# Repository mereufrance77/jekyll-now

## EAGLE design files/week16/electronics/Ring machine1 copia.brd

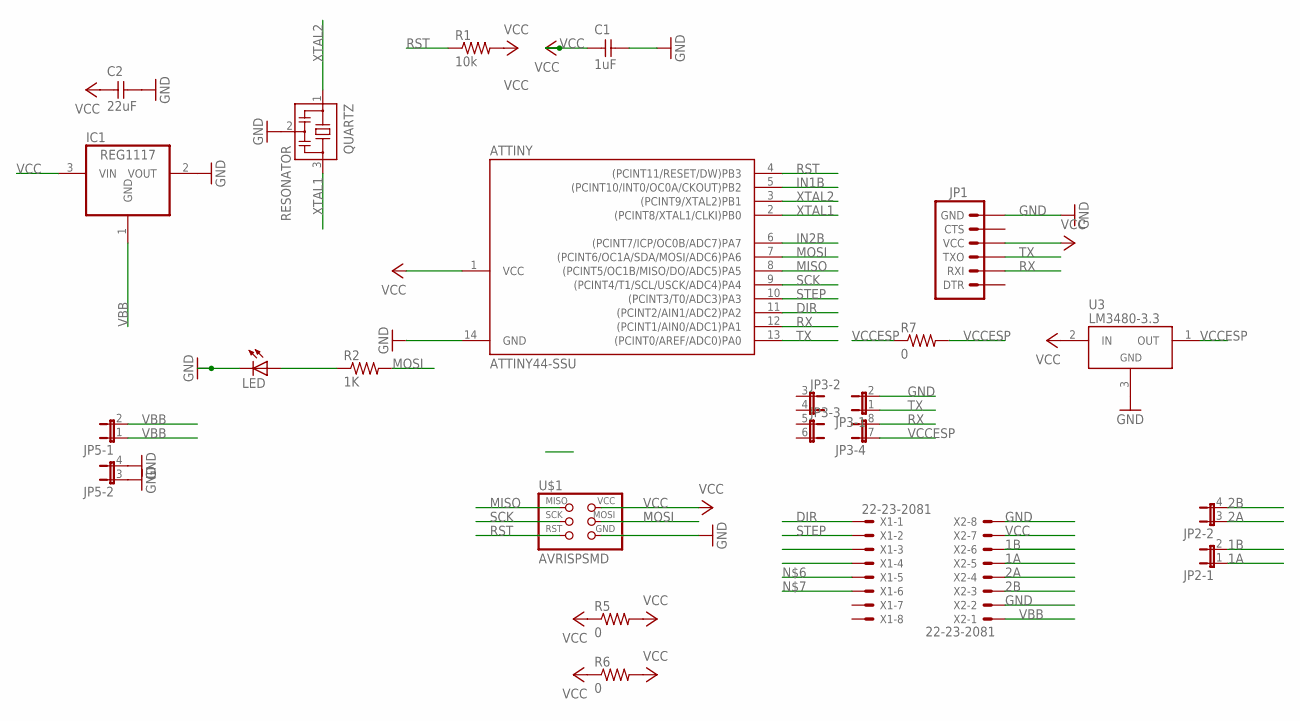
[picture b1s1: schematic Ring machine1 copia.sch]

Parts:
ATTINY: ATTINY44-SSU; SOIC14
C1: 1uF; 1206
C2: 22uF; 1206
IC1: REG1117; SOT223
JP1: ARDUINO_SERIAL_PROGRAMLONGPADS; 1X06_LONGPADS
JP2, JP5: JP2QE; JP2Q
JP3: JP4QE; JP4Q
LED: LED1206; 1206
QUARTZ: RESONATOR; EFOBM
R1: 10k; 1206
R2: 1K; 1206
R5, R6, R7: 0; 1206
U3: LM3480-3.3; SOT-23-3
U$1: AVRISPSMD; 2X03SMD
X1, X2: 22-23-2081

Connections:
1A: JP2.1, X2.5
1B: JP2.2, X2.6
2A: JP2.3 (1), X2.4
2B: JP2.4 (2), X2.3
DIR: ATTINY.11 ((PCINT2/AIN1/ADC2)PA2), X1.1
GND: ATTINY.14 (GND), C1.2, C2.2, IC1.2 (VOUT), JP1.6 (GND), JP3.2, JP5.3 (1), JP5.4 (2), LED.2 (C), QUARTZ.2, U3.3 (GND), U$1.6 (GND), X2.2, X2.8
IN1B: ATTINY.5 ((PCINT10/INT0/OC0A/CKOUT)PB2)
IN2B: ATTINY.6 ((PCINT7/ICP/OC0B/ADC7)PA7)
LEDRES: LED.1 (A), R2.1
MISO: ATTINY.8 ((PCINT5/OC1B/MISO/DO/ADC5)PA5), U$1.1 (MISO)
MOSI: ATTINY.7 ((PCINT6/OC1A/SDA/MOSI/ADC6)PA6), R2.2, U$1.4 (MOSI)
RST: ATTINY.4 ((PCINT11/RESET/DW)PB3), R1.1, U$1.5 (RST)
RX: ATTINY.12 ((PCINT1/AIN0/ADC1)PA1), JP1.2 (RXI), JP3.8 (2)
SCK: ATTINY.9 ((PCINT4/T1/SCL/USCK/ADC4)PA4), U$1.3 (SCK)
STEP: ATTINY.10 ((PCINT3/T0/ADC3)PA3), X1.2
TX: ATTINY.13 ((PCINT0/AREF/ADC0)PA0), JP1.3 (TXO), JP3.1
VBB: IC1.1 (GND), JP5.1, JP5.2, X2.1
VCC: ATTINY.1 (VCC), C1.1, C2.1, IC1.3 (VIN), JP1.4 (VCC), R1.2, R5.1, R5.2, R6.1, R6.2, U3.2 (IN), U$1.2 (VCC), X2.7
VCCESP: JP3.7 (1), R7.1, R7.2, U3.1 (OUT)
XTAL1: ATTINY.2 ((PCINT8/XTAL1/CLKI)PB0), QUARTZ.3
XTAL2: ATTINY.3 ((PCINT9/XTAL2)PB1), QUARTZ.1

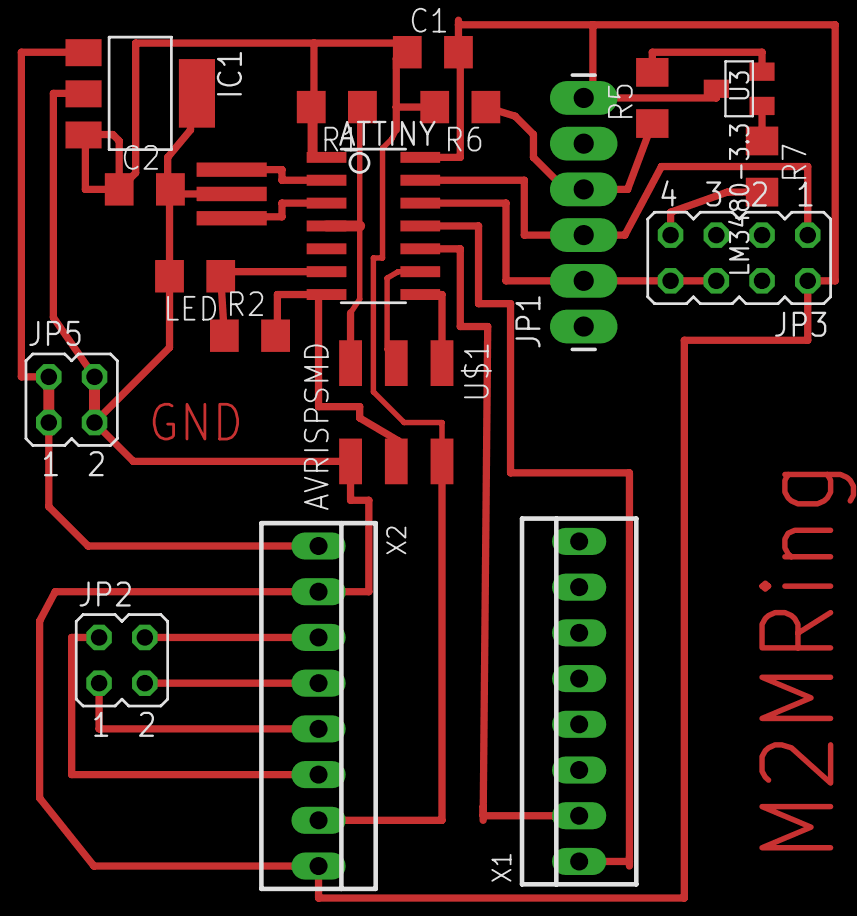
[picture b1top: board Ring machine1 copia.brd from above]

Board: 2 copper layers, 19 parts (0 on the bottom side), 19 nets.

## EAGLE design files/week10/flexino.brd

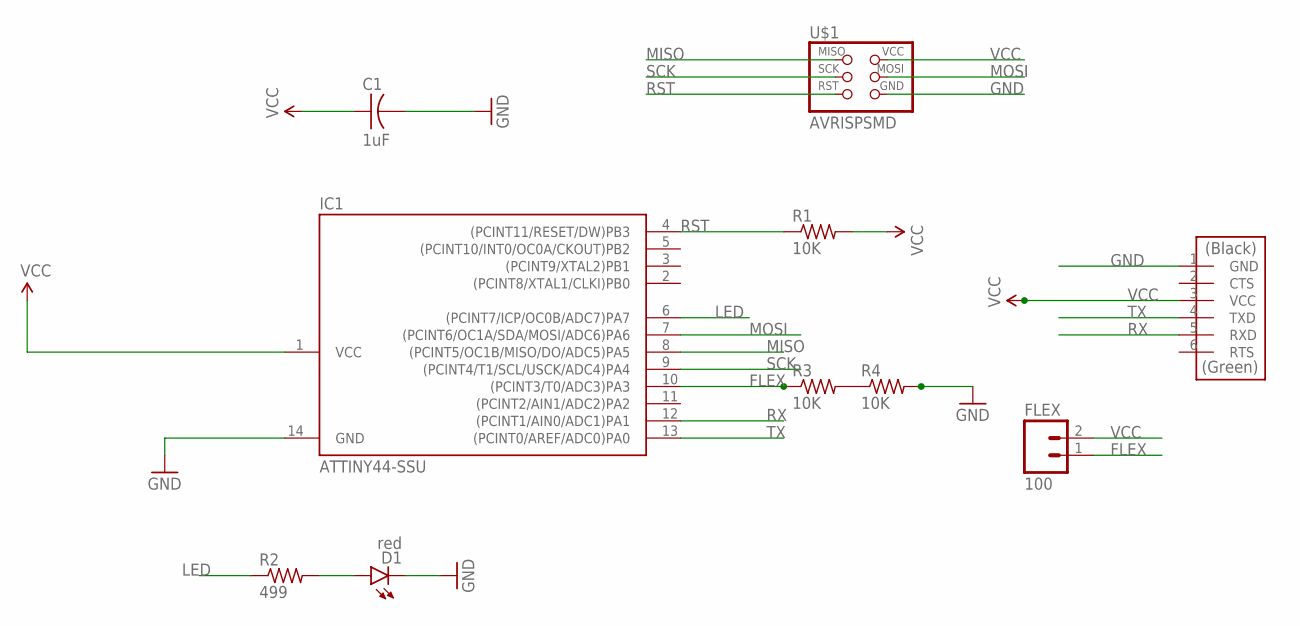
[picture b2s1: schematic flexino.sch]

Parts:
C1: 1uF; C1206FAB
D1: red; LED-1206
FLEX: 100; 1X02_LONGPADS
IC1: ATTINY44-SSU; SOIC14
R1, R3, R4: 10K; R1206W
R2: 499; R1206W
U$1: AVRISPSMD; 2X03SMD
U$2: FTDI-SMD-HEADER; 1X06SMD

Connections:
FLEX: FLEX.1, IC1.10 ((PCINT3/T0/ADC3)PA3), R3.1
GND: C1.2, D1.C, IC1.14 (GND), R4.2, U$1.6 (GND), U$2.1 (GND)
LED: IC1.6 ((PCINT7/ICP/OC0B/ADC7)PA7), R2.1
MISO: IC1.8 ((PCINT5/OC1B/MISO/DO/ADC5)PA5), U$1.1 (MISO)
MOSI: IC1.7 ((PCINT6/OC1A/SDA/MOSI/ADC6)PA6), U$1.4 (MOSI)
unnamed: D1.A, R2.2
unnamed: R3.2, R4.1
RST: IC1.4 ((PCINT11/RESET/DW)PB3), R1.1, U$1.5 (RST)
RX: IC1.12 ((PCINT1/AIN0/ADC1)PA1), U$2.5 (RXD)
SCK: IC1.9 ((PCINT4/T1/SCL/USCK/ADC4)PA4), U$1.3 (SCK)
TX: IC1.13 ((PCINT0/AREF/ADC0)PA0), U$2.4 (TXD)
VCC: C1.1, FLEX.2, IC1.1 (VCC), R1.2, U$1.2 (VCC), U$2.3 (VCC)

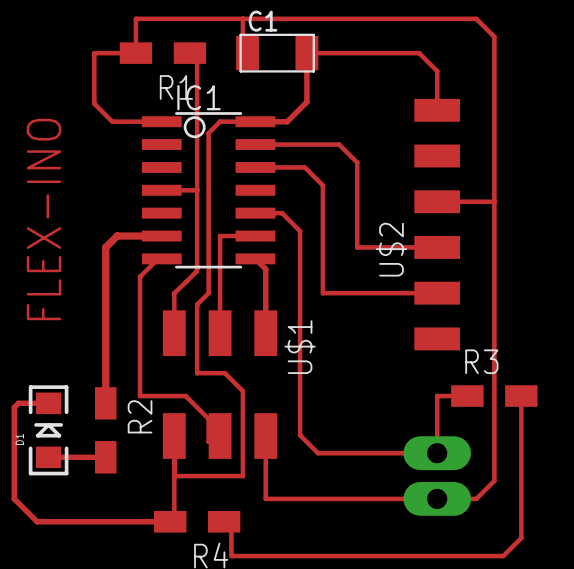
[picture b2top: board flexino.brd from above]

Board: 2 copper layers, 10 parts (0 on the bottom side), 12 nets.

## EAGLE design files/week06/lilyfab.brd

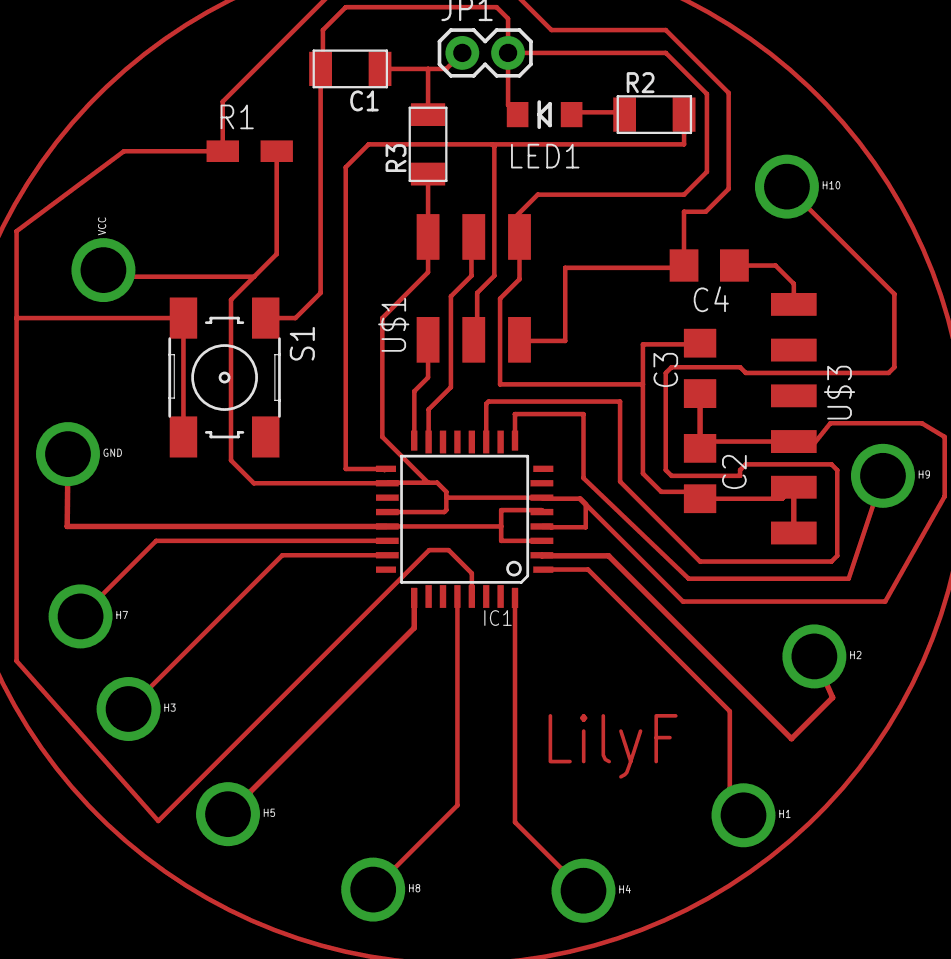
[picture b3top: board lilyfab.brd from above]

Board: 2 copper layers, 24 parts (0 on the bottom side), 18 nets.

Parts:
C1: 4uF; C1206FAB
C2: 1.0uF; C1206
C3: 0.1 uF; C1206
C4: 0.1uF; C1206
GND: SEW_HOLE; SIMPLE_HOLE
H1, H2, H3, H4, H5, H7, H8, H9, H10: SEW_HOLE; SIMPLE_HOLE
IC1: ATMEGA88-THIN; TQFP32-08THIN
JP1: 1X02
LED1: LED-1206
R1: 10K; R1206W
R2: 330; R1206FAB
R3: 0; R1206FAB
S1: 6MM_SWITCH
U$1: AVRISPSMD; 2X03SMD
U$3: FTDI-SMD-HEADER; 1X06SMD
VCC: SEW_HOLE; SIMPLE_HOLE

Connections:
GND: C1.2, C2.2, C3.2, JP1.2, LED1.C, S1.1, U$1.6, U$3.1, U$3.2
MISO: IC1.16, U$1.1
MOSI: IC1.15, U$1.4
unnamed: H3.P$1, IC1.23
unnamed: H7.P$1, IC1.22
unnamed: LED1.A, R2.1
unnamed: H5.P$1, IC1.25
unnamed: H8.P$1, IC1.28
unnamed: H4.P$1, IC1.32
unnamed: H1.P$1, IC1.1
unnamed: H2.P$1, IC1.2
unnamed: H9.P$1, IC1.9
unnamed: H10.P$1, IC1.11
unnamed: GND.P$1, IC1.3, IC1.5, IC1.21
RST: C4.2, IC1.29, R1.1, S1.3, S1.4, U$1.5
RTS: C4.1, U$3.6
SCK: IC1.17, R2.2, U$1.3
VCC: C1.1, C2.1, C3.1, IC1.4, IC1.6, IC1.18, IC1.20, JP1.1, R1.2, R3.1, R3.2, U$1.2, U$3.3, VCC.P$1

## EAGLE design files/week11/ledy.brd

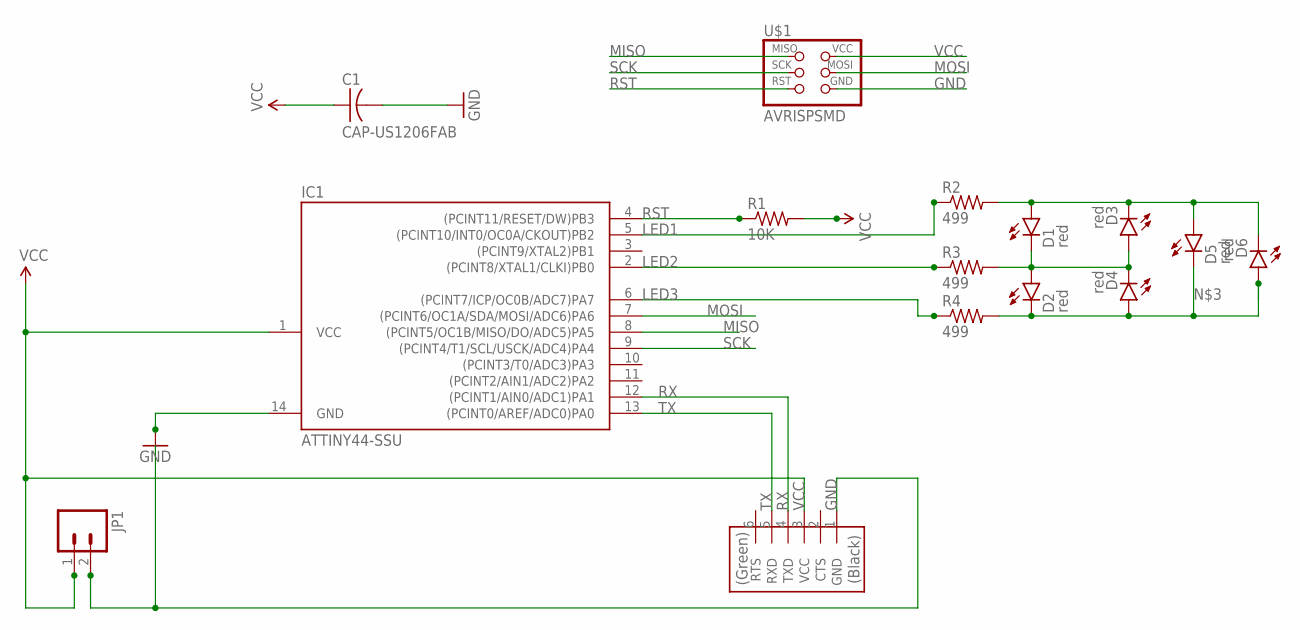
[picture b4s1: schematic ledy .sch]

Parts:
C1: CAP-US1206FAB; C1206FAB
D1, D2, D3, D4, D5, D6: red; LED-1206
IC1: ATTINY44-SSU; SOIC14
JP1: M02PTH; 1X02
R1: 10K; R1206W
R2, R3, R4: 499; R1206W
U$1: AVRISPSMD; 2X03SMD
U$3: FTDI-SMD-HEADER; 1X06SMD

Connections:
GND: C1.2, IC1.14 (GND), JP1.2, U$1.6 (GND), U$3.1 (GND)
LED1: IC1.5 ((PCINT10/INT0/OC0A/CKOUT)PB2), R2.1
LED2: R3.1
LED3: IC1.6 ((PCINT7/ICP/OC0B/ADC7)PA7), R4.1
MISO: IC1.8 ((PCINT5/OC1B/MISO/DO/ADC5)PA5), U$1.1 (MISO)
MOSI: IC1.7 ((PCINT6/OC1A/SDA/MOSI/ADC6)PA6), U$1.4 (MOSI)
unnamed: D1.A, D3.C, D5.A, D6.C, R2.2
unnamed: D2.C, D4.A, D5.C, D6.A, R4.2
unnamed: D1.C, D2.A, D3.A, D4.C, R3.2
RST: IC1.4 ((PCINT11/RESET/DW)PB3), R1.1, U$1.5 (RST)
RX: IC1.12 ((PCINT1/AIN0/ADC1)PA1), U$3.4 (TXD)
SCK: IC1.9 ((PCINT4/T1/SCL/USCK/ADC4)PA4), U$1.3 (SCK)
TX: IC1.13 ((PCINT0/AREF/ADC0)PA0), U$3.5 (RXD)
VCC: C1.1, IC1.1 (VCC), JP1.1, R1.2, U$1.2 (VCC), U$3.3 (VCC)

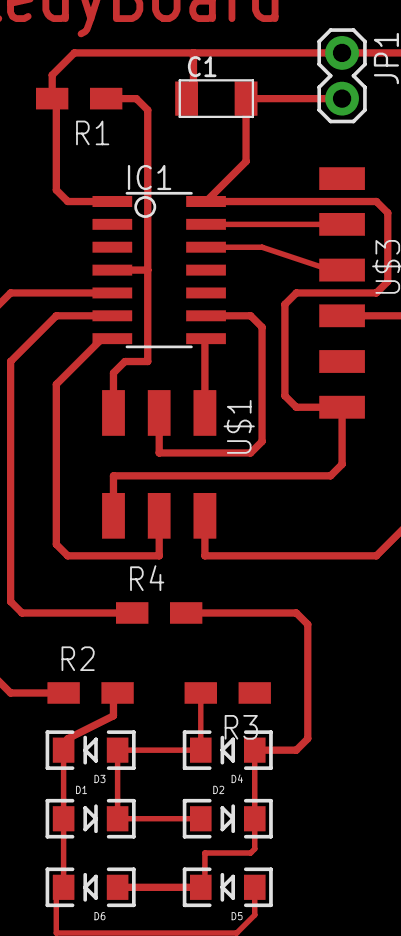
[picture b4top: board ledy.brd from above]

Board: 2 copper layers, 15 parts (0 on the bottom side), 13 nets.

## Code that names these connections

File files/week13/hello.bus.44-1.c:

//
//
// hello.bus.44.c
//
// 9600 baud serial bus hello-world
//
// Neil Gershenfeld
// 11/24/10
//
// (c) Massachusetts Institute of Technology 2010
// Permission granted for experimental and personal use;
// license for commercial sale available from MIT.
//

#include <avr/io.h>
#include <util/delay.h>
#include <avr/pgmspace.h>
#include <string.h>

#define output(directions,pin) (directions |= pin) // set port direction for output
#define input(directions,pin) (directions &= (~pin)) // set port direction for input
#define set(port,pin) (port |= pin) // set port pin
#define clear(port,pin) (port &= (~pin)) // clear port pin
#define pin_test(pins,pin) (pins & pin) // test for port pin
#define bit_test(byte,bit) (byte & (1 << bit)) // test for bit set
#define bit_delay_time 100 // bit delay for 9600 with overhead
#define bit_delay() _delay_us(bit_delay_time) // RS232 bit delay
#define half_bit_delay() _delay_us(bit_delay_time/2) // RS232 half bit delay
#define led_delay() _delay_ms(100) // LED flash delay

#define led_port PORTA
#define led_direction DDRA
#define led_pin (1 << PA7)

#define serial_port PORTB
#define serial_direction DDRB
#define serial_pins PINB
#define serial_pin_in (1 << PB0)
#define serial_pin_out (1 << PB1)

#define node_id '1'

void get_char(volatile unsigned char *pins, unsigned char pin, char *rxbyte) {
   //
   // read character into rxbyte on pins pin
   //    assumes line driver (inverts bits)
   //
   *rxbyte = 0;
   while (pin_test(*pins,pin))
      //
      // wait for start bit
      //
      ;
   //
   // delay to middle of first data bit
   //
   half_bit_delay();
   bit_delay();
   //
   // unrolled loop to read data bits
   //
   if pin_test(*pins,pin)
      *rxbyte |= (1 << 0);
   else
      *rxbyte |= (0 << 0);
   bit_delay();
   if pin_test(*pins,pin)
      *rxbyte |= (1 << 1);
   else
      *rxbyte |= (0 << 1);
   bit_delay();
   if pin_test(*pins,pin)
      *rxbyte |= (1 << 2);
   else
      *rxbyte |= (0 << 2);
   bit_delay();
   if pin_test(*pins,pin)
      *rxbyte |= (1 << 3);
   else
      *rxbyte |= (0 << 3);
   bit_delay();
   if pin_test(*pins,pin)
      *rxbyte |= (1 << 4);
   else
      *rxbyte |= (0 << 4);
   bit_delay();
   if pin_test(*pins,pin)
      *rxbyte |= (1 << 5);
   else
      *rxbyte |= (0 << 5);
   bit_delay();
   if pin_test(*pins,pin)
      *rxbyte |= (1 << 6);
   else
      *rxbyte |= (0 << 6);
   bit_delay();
   if pin_test(*pins,pin)
      *rxbyte |= (1 << 7);
   else
      *rxbyte |= (0 << 7);
   //
   // wait for stop bit
   //
   bit_delay();
   half_bit_delay();
   }

void put_char(volatile unsigned char *port, unsigned char pin, char txchar) {
   //
   // send character in txchar on port pin
   //    assumes line driver (inverts bits)
   //
   // start bit
   //
   clear(*port,pin);
   bit_delay();
   //
   // unrolled loop to write data bits
   //
   if bit_test(txchar,0)
      set(*port,pin);
   else
      clear(*port,pin);
   bit_delay();
   if bit_test(txchar,1)
      set(*port,pin);
   else
      clear(*port,pin);
   bit_delay();
   if bit_test(txchar,2)
      set(*port,pin);
   else
      clear(*port,pin);
   bit_delay();
   if bit_test(txchar,3)
      set(*port,pin);
   else
      clear(*port,pin);
   bit_delay();
   if bit_test(txchar,4)
      set(*port,pin);
   else
      clear(*port,pin);
   bit_delay();
   if bit_test(txchar,5)
      set(*port,pin);
   else
      clear(*port,pin);
   bit_delay();
   if bit_test(txchar,6)
      set(*port,pin);
   else
      clear(*port,pin);
   bit_delay();
   if bit_test(txchar,7)
      set(*port,pin);
   else
      clear(*port,pin);
   bit_delay();
   //
   // stop bit
   //
   set(*port,pin);
   bit_delay();
   //
   // char delay
   //
   bit_delay();
   }

void put_string(volatile unsigned char *port, unsigned char pin, PGM_P str) {
   //
   // send character in txchar on port pin
   //    assumes line driver (inverts bits)
   //
   static char chr;
   static int index;
   index = 0;//
//
// hello.Flex.44.c
//
// flex sensor hello-world
//    9600 baud FTDI interface
//
// Francesca Mereu
// 10/05/15
//
// (c) Massachusetts Institute of Technology 2015
// This work may be reproduced, modified, distributed,
// performed, and displayed for any purpose. Copyright is
// retained and must be preserved. The work is provided
// as is; no warranty is provided, and users accept all 
// liability.
//

#include <avr/io.h>
#include <util/delay.h>

#define output(directions,pin) (directions |= pin) // set port direction for output
#define set(port,pin) (port |= pin) // set port pin
#define clear(port,pin) (port &= (~pin)) // clear port pin
#define pin_test(pins,pin) (pins & pin) // test for port pin
#define bit_test(byte,bit) (byte & (1 << bit)) // test for bit set
#define bit_delay_time 102 // bit delay for 9600 with overhead
#define bit_delay() _delay_us(bit_delay_time) // RS232 bit delay
#define half_bit_delay() _delay_us(bit_delay_time/2) // RS232 half bit delay
#define char_delay() _delay_ms(10) // char delay

#define serial_port PORTA
#define serial_direction DDRA
#define serial_pin_out (1 << PA3)

void put_char(volatile unsigned char *port, unsigned char pin, char txchar) {
   //
   // send character in txchar on port pin
   //    assumes line driver (inverts bits)
   //
   // start bit
   //
   clear(*port,pin);
   bit_delay();
   //
   // unrolled loop to write data bits
   //
   if bit_test(txchar,0)
      set(*port,pin);
   else
      clear(*port,pin);
   bit_delay();
   if bit_test(txchar,1)
      set(*port,pin);
   else
      clear(*port,pin);
   bit_delay();
   if bit_test(txchar,2)
      set(*port,pin);
   else
      clear(*port,pin);
   bit_delay();
   if bit_test(txchar,3)
      set(*port,pin);
   else
      clear(*port,pin);
   bit_delay();
   if bit_test(txchar,4)
      set(*port,pin);
   else
      clear(*port,pin);
   bit_delay();
   if bit_test(txchar,5)
      set(*port,pin);
   else
      clear(*port,pin);
   bit_delay();
   if bit_test(txchar,6)
      set(*port,pin);
   else
      clear(*port,pin);
   bit_delay();
   if bit_test(txchar,7)
      set(*port,pin);
   else
      clear(*port,pin);
   bit_delay();
   //
   // stop bit
   //
   set(*port,pin);
   bit_delay();
   //
   // char delay
   //
   bit_delay();
   }

int main(void) {
   //
   // main
   //
   static char chr;
   //
   // set clock divider to /1
   //
   CLKPR = (1 << CLKPCE);
   CLKPR = (0 << CLKPS3) | (0 << CLKPS2) | (0 << CLKPS1) | (0 << CLKPS0);
   //
   // initialize output pins
   //
   set(serial_port, serial_pin_out);
   output(serial_direction, serial_pin_out);
   //
   // init A/D
   //
   ADMUX = (0 << REFS1) | (0 << REFS0) // Vcc ref
      | (0 << ADLAR) // right adjust
      |(0 << MUX5) | (0 << MUX4) | (0 << MUX3) | (0 << MUX2) | (1 << MUX1) | (1 << MUX0); // ADC3
   ADCSRA = (1 << ADEN) // enable
      | (1 << ADPS2) | (1 << ADPS1) | (1 << ADPS0); // prescaler /128
   //
   // main loop
   //
   while (1) {
      //
      // send framing
      //
      put_char(&serial_port, serial_pin_out, 1);
      char_delay();
      put_char(&serial_port, serial_pin_out, 2);
      char_delay();
      put_char(&serial_port, serial_pin_out, 3);
      char_delay();
      put_char(&serial_port, serial_pin_out, 4);
      char_delay();
      //
      // initiate conversion
      //
      ADCSRA |= (1 << ADSC);
      //
      // wait for completion
      //
      while (ADCSRA & (1 << ADSC))
         ;
      //
      // send result
      //
      chr = ADCL;
      put_char(&serial_port, serial_pin_out, chr);
      char_delay();
      chr = ADCH;
      put_char(&serial_port, serial_pin_out, chr);
      char_delay();
      }
   }

   do {
      chr = pgm_read_byte(&(str[index]));
      put_char(&serial_port, serial_pin_out, chr);
      ++index;
      } while (chr != 0);
   }

void flash() {
   //
   // LED flash delay
   //
   clear(led_port, led_pin);
   led_delay();
   set(led_port, led_pin);
   }

int main(void) {
   //
   // main
   //
   static char chr;
   //
   // set clock divider to /1
   //
   CLKPR = (1 << CLKPCE);
   CLKPR = (0 << CLKPS3) | (0 << CLKPS2) | (0 << CLKPS1) | (0 << CLKPS0);
   //
   // initialize output pins
   //
   set(serial_port, serial_pin_out);
   input(serial_direction, serial_pin_out);
   set(led_port, led_pin);
   output(led_direction, led_pin);
   //
   // main loop
   //
   while (1) {
      get_char(&serial_pins, serial_pin_in, &chr);
      flash();
      if (chr == node_id) {
         output(serial_direction, serial_pin_out);
         static char message[] PROGMEM = "node ";
         put_string(&serial_port, serial_pin_out, (PGM_P) message);
         put_char(&serial_port, serial_pin_out, chr);
         put_char(&serial_port, serial_pin_out, 10); // new line
         led_delay();
         flash();
         input(serial_direction, serial_pin_out);
         }
      }
   }

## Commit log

2015-01-22 Rename 2014-3-3-Hello-World.md to 2015-1-22-Hello-World.md
2015-01-23 Create project
2015-01-23 Create _project
2015-01-28 first upload
2015-01-28 clean site
2015-01-28 add new site
2015-01-28 aggiornato sito
2015-01-28 aggiorna sito
2015-01-30 sync
2015-02-13 aggiornata struttura sito
2015-03-25 Rewrite the class 8 -mit message for your changes. Lines starting
    Regenerating the past classes
    delete posts
    Insert new post about the last class: computer controlled machining
    insert new images
2015-03-25 corretto index
2015-03-25 reset

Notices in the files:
parts and their libraries:
SparkFun-Connectors: Licensing: Creative Commons ShareAlike 4.0 International - https://creativecommons.org/licenses/by-sa/4.0
